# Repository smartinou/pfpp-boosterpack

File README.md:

# pfpp-rtcc-boosterpack
A boosterpack-compatible board for pfpp project.

This board holds a battery-backup'ed precision RTCC. It's main duty is to keep the time of the day and manage alarms that are set for feeding your pet.

on top of an RTCC, it also holds a MicroSD card cage, and a TB6612 motor controller. The MicroSD card can be used for logging events. The motor controller is used to activate the feeder.

This project was originally built for the EK-TM4C129EXL development board, on boosterpack2 location. It should work on any BoosterPack-compatible interface.

## GPIO Mapping

GPIO match for various development boards.

### EK-TM4C129EXL

J1
Pin | MCU Pin | BoosterPack Schematic
--- | --- | ---
1 | +3.3V | +3.3V
2 | PD2 | NC
3 | PP0 | NC
4 | PP1 | NC
5 | See JP4 | SPI_SDC_CSn
6 | See JP5 | NC
7 | PQ0 | SPI_CLK
8 | PP4 | NC
9 | PN5 | NC
10 | PN4 | NC

J2
Pin | MCU Pin | BoosterPack Schematic
--- | --- | ---
1 | GND | GND
2 | PM7 | NC
3 | PP5 | NC
4 | PA7 | SD_DET
5 | Reset | NC
6 | PQ2/PA3 | SPI_MOSI
7 | PQ3/PA2 | SPI_MISO
8 | PP3 | RTCC_INTn
9 | PQ1 | SPI_RTCC_CSn
10 | PM6 | AIN2

J3
Pin | MCU Pin | BoosterPack Schematic
--- | --- | ---
1 | +5V | NC
2 | GND | GND
3 | PB4 | NC
4 | PB5 | NC
5 | PK0 | NC
6 | PK1 | NC
7 | PK2 | NC
8 | PK3 | NC
9 | PA4 | NC
10 | PA5 | NC

J4
Pin | MCU Pin | BoosterPack Schematic
--- | --- | ---
1 | PG1 | PWMB
2 | PK4 | PWMA
3 | PK5 | NC
4 | PM0 | NC
5 | PM1 | NC
6 | PM2 | BIN2
7 | PH0 | BIN1
8 | PH1 | STBYn
9 | PK6 | AIN1
10 | PK7 | RTCC_RST

### EK-TM4C123GXL

**Even if the board was 1st developed for the EK-TM4C129EXL, the GPIO pin matching for the EK-TM4C123GXL corresponds to the symbols in the schematic.**

Pin | J1 MCU Pin | J1 BoosterPack Schematic | J3 MCU Pin | J3 BoosterPack Schematic
--- | --- | --- | --- | ---
1 | +3.3V | +3.3V | +5V | NC
2 | PB5 | NC | GND | GND
3 | PB0 | NC | PB4 | NC
4 | PB1 | NC | PB5 | NC
5 | PE4 | SPI_SDC_CSn | PK0 | NC
6 | PE5 | NC | PK1 | NC
7 | PB4 | SPI_CLK | PK2 | NC
8 | PA5 | NC | PK3 | NC
9 | PA6 | NC | PA4 | NC
10 | PA6 | NC | PA5 | NC

Pin | J4 MCU Pin | J4 BoosterPack Schematic | J2 MCU Pin | J2 BoosterPack Schematic
--- | --- | --- | --- | ---
1 | PF2 | PWMB | GND | GND
2 | PF3 | PWMA | PB2 | NC
3 | PB3 | NC | PB0 | NC
4 | PC4 | NC | PF0 | SD_DET
5 | PC5 | NC | Reset | NC
6 | PC6 | BIN2 | PB7 | SPI_MOSI
7 | PC7 | BIN1 | PB6 | SPI_MISO
8 | PD6 | STBYn | PA4 | RTCC_INTn
9 | PD7 | AIN1 | PA3 | SPI_RTCC_CSn
10 | PC4 | RTCC_RST | PA2 | AIN2

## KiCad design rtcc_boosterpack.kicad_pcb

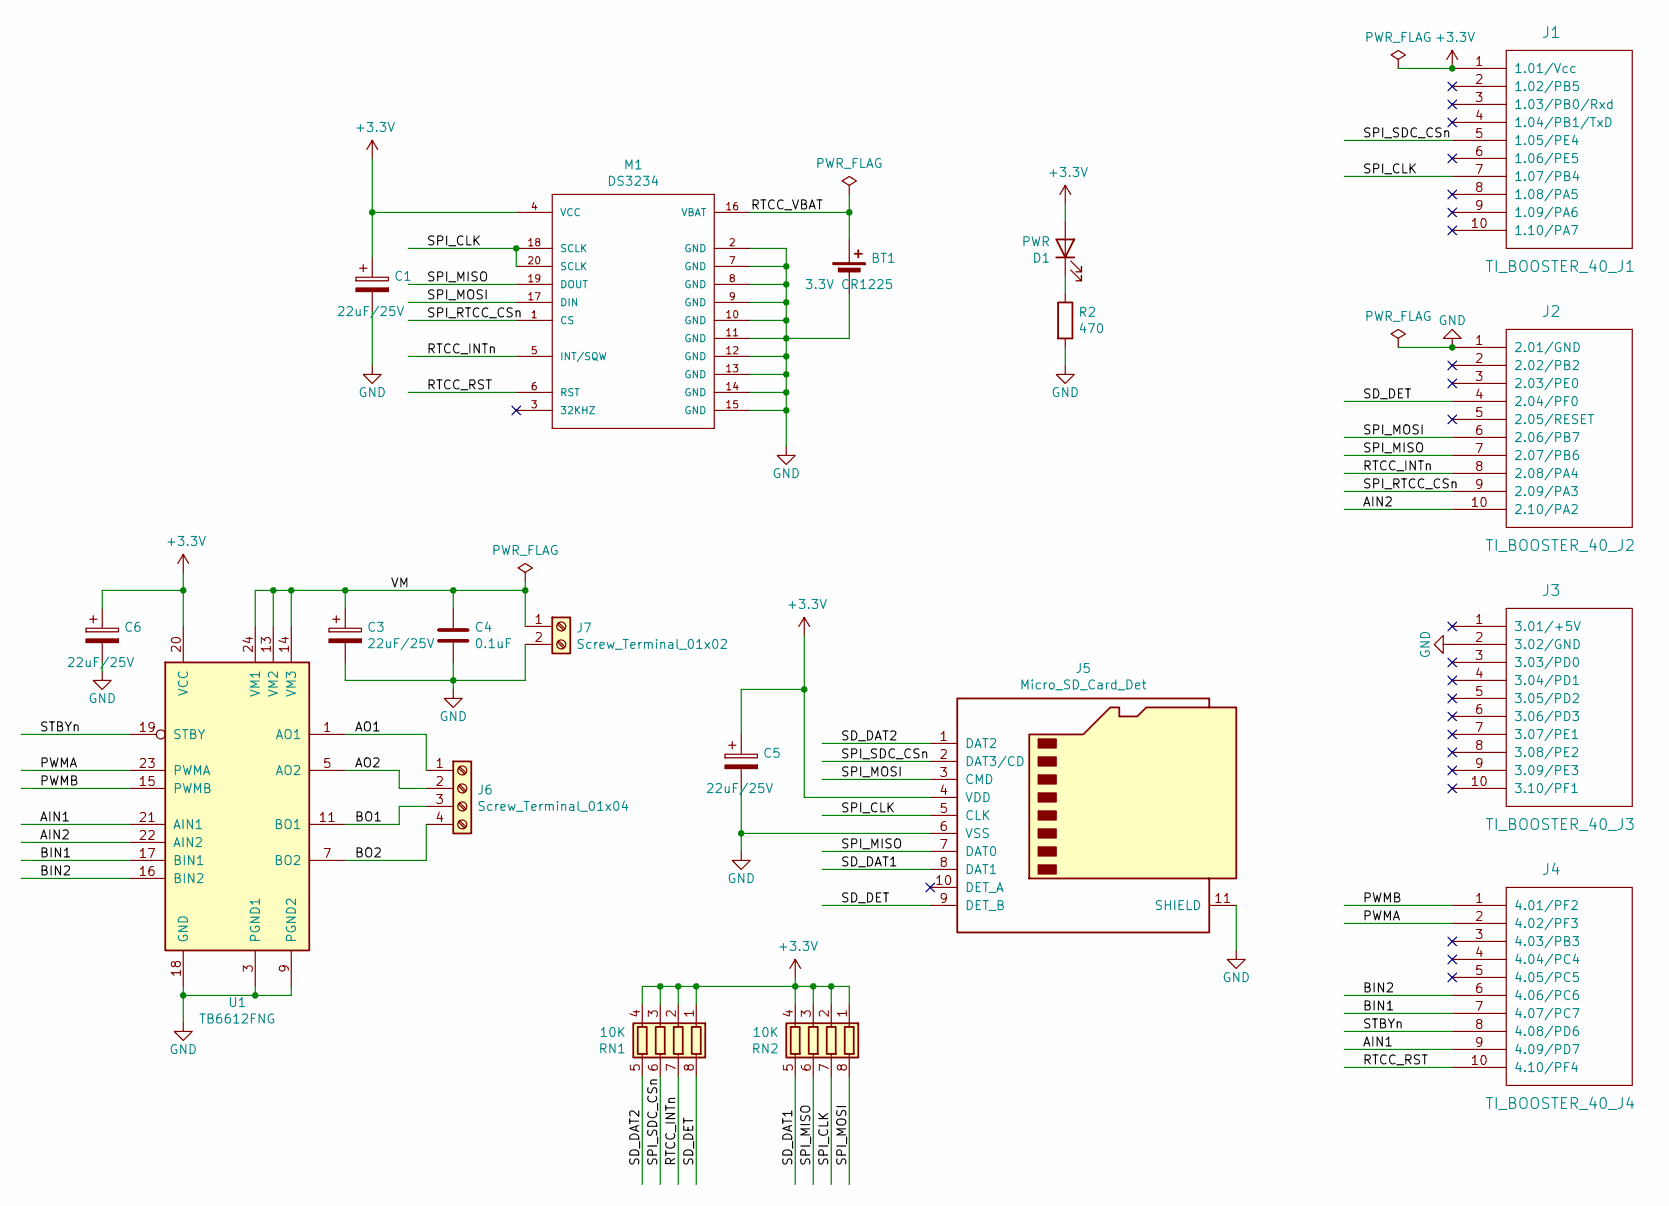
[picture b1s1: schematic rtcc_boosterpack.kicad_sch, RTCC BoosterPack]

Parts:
BT1: 3.3V CR1225; BatteryHolder_Keystone_3000_1x12mm; LCSC N/A
C1, C3, C5, C6: 22uF/25V; C_0805_2012Metric_Pad1.18x1.45mm_HandSolder; LCSC C45783
C4: 0.1uF; C_0603_1608Metric_Pad1.08x0.95mm_HandSolder; LCSC C14663
D1: PWR; LED_0603_1608Metric_Pad1.05x0.95mm_HandSolder; LCSC C2286
J1: TI_BOOSTER_40_J1; PinHeader_1x10_P2.54mm_Vertical; LCSC N/A
J2: TI_BOOSTER_40_J2; PinHeader_1x10_P2.54mm_Vertical; LCSC N/A
J3: TI_BOOSTER_40_J3; PinHeader_1x10_P2.54mm_Vertical; LCSC N/A
J4: TI_BOOSTER_40_J4; PinHeader_1x10_P2.54mm_Vertical; LCSC N/A
J5: Micro_SD_Card_Det; SF-MICRO-SD-PFPP; LCSC C105419
J6: Screw_Terminal_01x04; TerminalBlock_TE_282834-4_1x04_P2.54mm_Horizontal; LCSC C474922
J7: Screw_Terminal_01x02; TerminalBlock_TE_282834-2_1x02_P2.54mm_Horizontal; LCSC C474920
M1: DS3234; SOP-20_7.5x12.8mm_P1.27mm; LCSC C143318
R2: 470; R_0603_1608Metric_Pad0.98x0.95mm_HandSolder; LCSC C23179
RN1, RN2: 10K; R_Array_Convex_4x0603; LCSC C29718
U1: TB6612FNG; TSSOP-24_6.1x7.8mm_P0.65mm; LCSC C141517

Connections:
+3V3: C1.1, C5.1, C6.1, D1.2 (A), J1.1 (1.01/Vcc), J5.4 (VDD), M1.4 (VCC), RN1.1 (R1.1), RN1.2 (R2.1), RN1.3 (R3.1), RN1.4 (R4.1), RN2.1 (R1.1), RN2.2 (R2.1), RN2.3 (R3.1), RN2.4 (R4.1), U1.20 (VCC)
/AIN1: J4.9 (4.09/PD7), U1.21 (AIN1)
/AIN2: J2.10 (2.10/PA2), U1.22 (AIN2)
/AO1: J6.1, U1.1 (AO1), U1.2 (AO1)
/AO2: J6.2, U1.5 (AO2), U1.6 (AO2)
/BIN1: J4.7 (4.07/PC7), U1.17 (BIN1)
/BIN2: J4.6 (4.06/PC6), U1.16 (BIN2)
/BO1: J6.3, U1.11 (BO1), U1.12 (BO1)
/BO2: J6.4, U1.7 (BO2), U1.8 (BO2)
/PWMA: J4.2 (4.02/PF3), U1.23 (PWMA)
/PWMB: J4.1 (4.01/PF2), U1.15 (PWMB)
/RTCC_INTn: J2.8 (2.08/PA4), M1.5 (INT/SQW), RN1.7 (R2.2)
/RTCC_RST: J4.10 (4.10/PF4), M1.6 (RST)
/RTCC_VBAT: BT1.1 (+), M1.16 (VBAT)
/SD_DAT1: J5.8 (DAT1), RN2.5 (R4.2)
/SD_DAT2: J5.1 (DAT2), RN1.5 (R4.2)
/SD_DET: J2.4 (2.04/PF0), J5.9 (DET_B), RN1.8 (R1.2)
/SPI_CLK: J1.7 (1.07/PB4), J5.5 (CLK), M1.18 (SCLK), M1.20 (SCLK), RN2.7 (R2.2)
/SPI_MISO: J2.7 (2.07/PB6), J5.7 (DAT0), M1.19 (DOUT), RN2.6 (R3.2)
/SPI_MOSI: J2.6 (2.06/PB7), J5.3 (CMD), M1.17 (DIN), RN2.8 (R1.2)
/SPI_RTCC_CSn: J2.9 (2.09/PA3), M1.1 (CS)
/SPI_SDC_CSn: J1.5 (1.05/PE4), J5.2 (DAT3/CD), RN1.6 (R3.2)
/STBYn: J4.8 (4.08/PD6), U1.19 (STBY)
/VM: C3.1, C4.1, J7.1, U1.13 (VM2), U1.14 (VM3), U1.24 (VM1)
GND: BT1.2 (-), C1.2, C3.2, C4.2, C5.2, C6.2, J2.1 (2.01/GND), J3.2 (3.02/GND), J5.6 (VSS), J5.11 (SHIELD), J7.2, M1.2 (GND), M1.7 (GND), M1.8 (GND), M1.9 (GND), M1.10 (GND), M1.11 (GND), M1.12 (GND), M1.13 (GND), M1.14 (GND), M1.15 (GND), R2.2, U1.3 (PGND1), U1.4 (PGND1), U1.9 (PGND2), U1.10 (PGND2), U1.18 (GND)
unnamed: D1.1 (K), R2.1

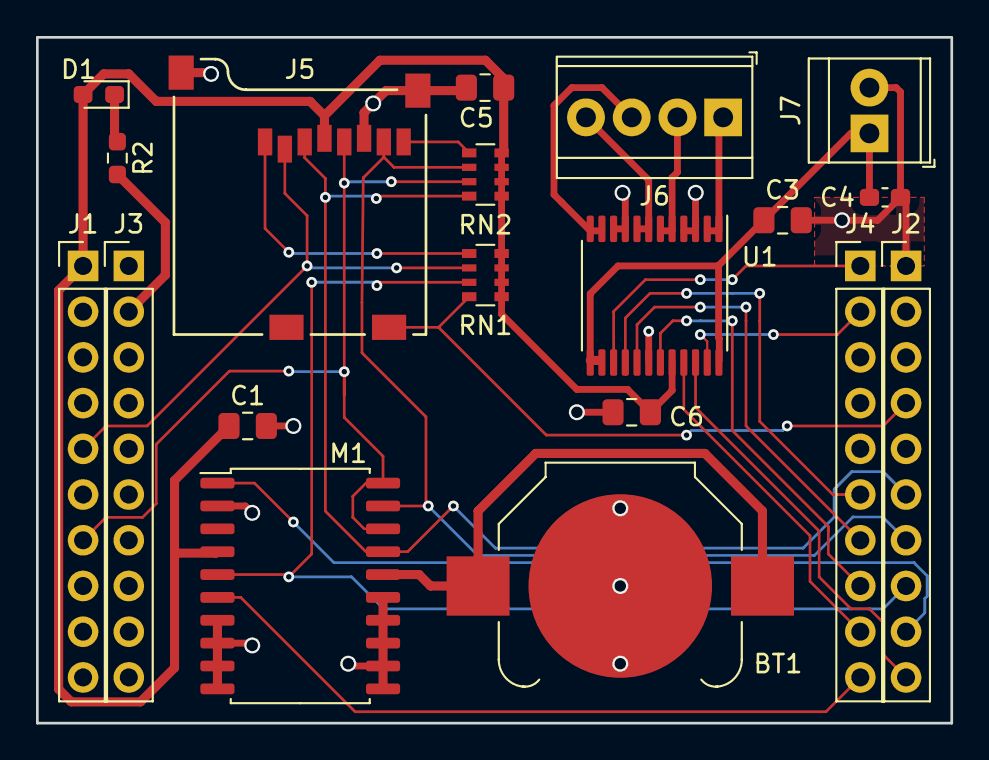
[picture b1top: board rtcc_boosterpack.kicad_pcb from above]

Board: 2 copper layers, 50.8 x 38.1 mm, 19 parts (0 on the bottom side), 26 nets.

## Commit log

2023-10-17 Initial commit of project files done using KiCad 5.x
2023-10-17 Convert to KiCad v7.0.8
2023-10-17 Converts schematic to KiCad 7.0.8
2023-10-17 Fixes D1 polarity.
2023-10-17 Updates revision number in design sheet.
2023-10-18 Updates to README.md
    Adds GPIO mapping for ek-tm4c129exl.
2023-10-18 Updates version printed on bottom silk screen.
2023-10-18 Update README.md
    Adds gpio mapping for ek-tm4c123exl
2023-10-19 Update README.md
    Finishes the GPIO mapping of the EK-TM4C123GXL dev board.
